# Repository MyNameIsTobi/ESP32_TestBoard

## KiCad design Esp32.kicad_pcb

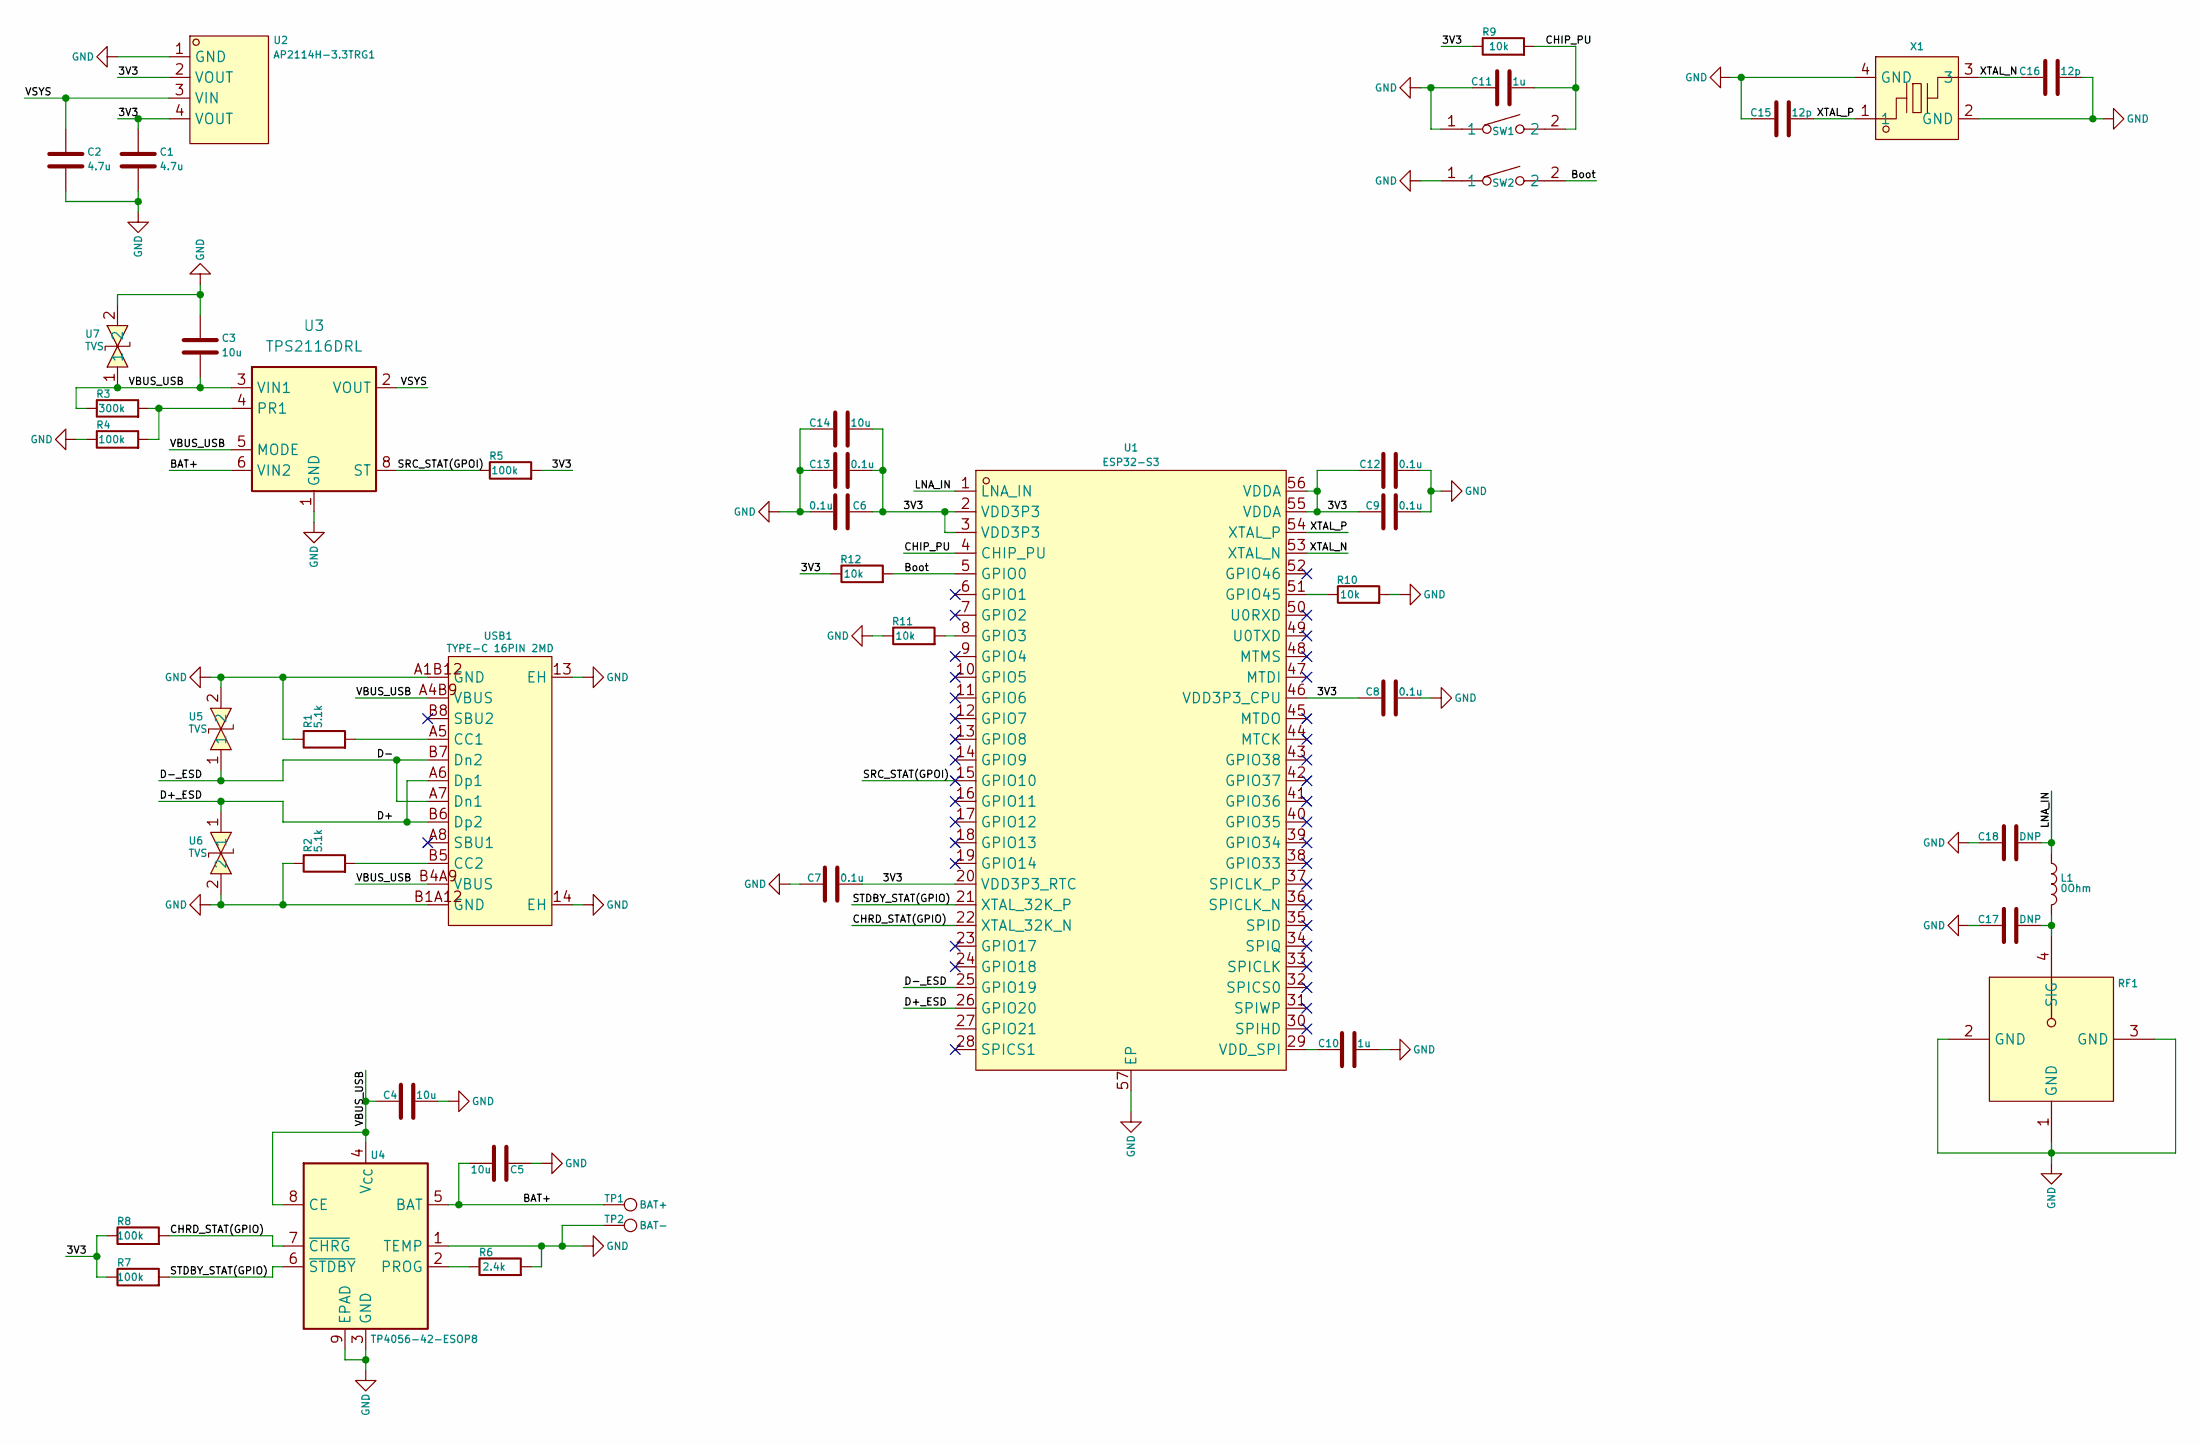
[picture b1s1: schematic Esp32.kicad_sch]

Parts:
C1, C2: 4.7u; C_0402_1005Metric
C3, C4, C5, C14: 10u; C_0402_1005Metric
C6, C7, C8, C9, C12, C13: 0.1u; C_0402_1005Metric
C10, C11: 1u; C_0402_1005Metric
C15, C16: 12p; C_0402_1005Metric
C17, C18: DNP; C_0402_1005Metric
L1: 0Ohm; R_0402_1005Metric
R1, R2: 5.1k; R_0402_1005Metric
R3: 300k; R_0402_1005Metric
R4, R5, R7, R8: 100k; R_0402_1005Metric
R6: 2.4k; R_0402_1005Metric
R9, R10, R11, R12: 10k; R_0402_1005Metric
RF1: KH-IPEX-K501-29; ANT-SMD_KH-IPEX-K501-29; MPN KH-IPEX-K501-29; LCSC Part C411563
SW1, SW2: TS-1088-AR02016; SW-SMD_L3.9-W3.0-P4.45; MPN TS-1088-AR02016; LCSC Part C720477
TP1: BAT+; TestPoint_Pad_D1.5mm
TP2: BAT-; TestPoint_Pad_D1.5mm
U1: ESP32-S3; QFN-56_L7.0-W7.0-P0.40-TL-EP4.0; MPN ESP32-S3FN8; LCSC Part C2913196
U2: AP2114H-3.3TRG1; SOT-223_L6.7-W3.5-P2.30-BR; MPN AP2114H-3.3TRG1; LCSC Part C150716
U3: TPS2116DRL; SOT-583-8
U4: TP4056-42-ESOP8; SOIC-8-1EP_3.9x4.9mm_P1.27mm_EP2.41x3.3mm_ThermalVias
U5, U6, U7: TVS; D0402-BI; MPN RCLAMP0521P.TCT-MS; LCSC Part C3029033
USB1: TYPE-C 16PIN 2MD; USB-C-SMD_TYPE-C-16PIN-2MD-073; MPN TYPE-C 16PIN 2MD(073); LCSC Part C2765186
X1: XTM32040000DT00351001; CRYSTAL-SMD_4P-L3.2-W2.5-BL-2; MPN XTM32040000DT00351001; LCSC Part C42464324

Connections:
/3V3: C1.1, C6.1, C7.1, C8.2, C9.2, C12.2, C13.1, C14.1, R5.2, R7.1, R8.1, R9.1, R12.1, U1.2 (VDD3P3), U1.3 (VDD3P3), U1.20 (VDD3P3_RTC), U1.46 (VDD3P3_CPU), U1.55 (VDDA), U1.56 (VDDA), U2.2 (VOUT), U2.4 (VOUT)
/BAT+: C5.1, TP1.1 (1_1), U3.6 (VIN2), U4.5 (BAT)
/Boot: R12.2, SW2.2, U1.5 (GPIO0)
/CHIP_PU: C11.1, R9.2, SW1.2, U1.4 (CHIP_PU)
/CHRD_STAT(GPIO): R8.2, U1.22 (XTAL_32K_N), U4.7 (~CHRG)
/D+: U1.26 (GPIO20), U6.1, USB1.A6 (Dp1), USB1.B6 (Dp2)
/D-: U1.25 (GPIO19), U5.1, USB1.A7 (Dn1), USB1.B7 (Dn2)
/LNA_IN: C18.1, L1.1, U1.1 (LNA_IN)
/SRC_STAT(GPOI): R5.1, U1.15 (GPIO10), U3.8 (ST)
/STDBY_STAT(GPIO): R7.2, U1.21 (XTAL_32K_P), U4.6 (~STDBY)
/VBUS_USB: C3.2, C4.2, R3.1, U3.3 (VIN1), U3.5 (MODE), U4.4 (V_{CC}), U4.8 (CE), U7.1, USB1.A4B9 (VBUS), USB1.B4A9 (VBUS)
/VSYS: C2.1, U2.3 (VIN), U3.2 (VOUT), U3.7 (VOUT)
/XTAL_N: C16.2, U1.53 (XTAL_N), X1.3
/XTAL_P: C15.1, U1.54 (XTAL_P), X1.1
GND: C1.2, C2.2, C3.1, C4.1, C5.2, C6.2, C7.2, C8.1, C9.1, C10.1, C11.2, C12.1, C13.2, C14.2, C15.2, C16.1, C17.2, C18.2, R1.1, R2.1, R4.1, R6.2, R10.2, R11.1, RF1.1 (GND), RF1.2 (GND), RF1.3 (GND), SW1.1, SW2.1, TP2.1 (1_1), U1.57 (EP), U2.1 (GND), U3.1 (GND), U4.1 (TEMP), U4.3 (GND), U4.9 (EPAD), U5.2, U6.2, U7.2, USB1.13 (EH), USB1.14 (EH), USB1.A1B12 (GND), USB1.B1A12 (GND), X1.2 (GND), X1.4 (GND)
unnamed: C17.1, L1.2, RF1.4 (SIG)
unnamed: R11.2, U1.8 (GPIO3)
unnamed: R10.1, U1.51 (GPIO45)
unnamed: C10.2, U1.29 (VDD_SPI)
unnamed: R3.2, R4.2, U3.4 (PR1)
unnamed: R6.1, U4.2 (PROG)
unnamed: R1.2, USB1.A5 (CC1)
unnamed: R2.2, USB1.B5 (CC2)

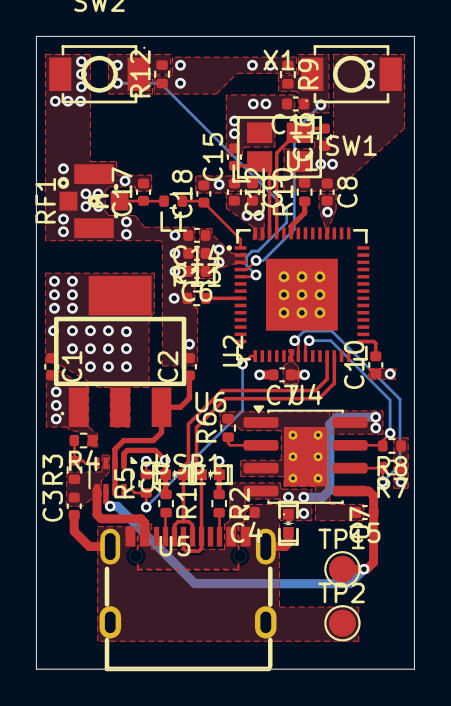
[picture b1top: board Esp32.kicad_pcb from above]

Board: 4 copper layers, 21.0 x 35.1 mm, 45 parts (0 on the bottom side), 23 nets.

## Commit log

2026-05-23 Initial commit: ESP32-S3FN8 test board skeleton
    KiCad project skeleton + gitignore for KiCad workflow.
    Target chip: ESP32-S3FN8 (QFN56, 8MB internal flash).
2026-05-23 Add ESP32-S3 datasheet + extracted reference DB
    PDF datasheet (v2.2) under datasheets/.
    Quick-lookup markdown reference under reference/, generated by
    4 parallel extraction agents covering pinout, strapping pins,
    electrical/RF specs, and package. Datasheet remains source of truth.
2026-05-29 Add USB-C connector with CC pulldowns + datasheet
    USB1 (TYPE-C 16PIN 2MD) placed and verified via netlist:
    - D+ net: U1.26 (GPIO20) + USB1.A6/B6 (Dp1/Dp2)
    - D- net: U1.25 (GPIO19) + USB1.A7/B7 (Dn1/Dn2)
    - CC1/CC2 pulled down via R1/R2 (5.1k each) to GND
    - GND on shield (13/14), A1B12, B1A12, U1.57 EP
    Still open at USB block: VBUS feed to LDO, ESD protection on D+/D-.
2026-06-04 kicad-sync: 2026-06-04T20:56:02Z on Mac
2026-06-08 kicad-sync: 2026-06-08T04:30:39Z on gaming
